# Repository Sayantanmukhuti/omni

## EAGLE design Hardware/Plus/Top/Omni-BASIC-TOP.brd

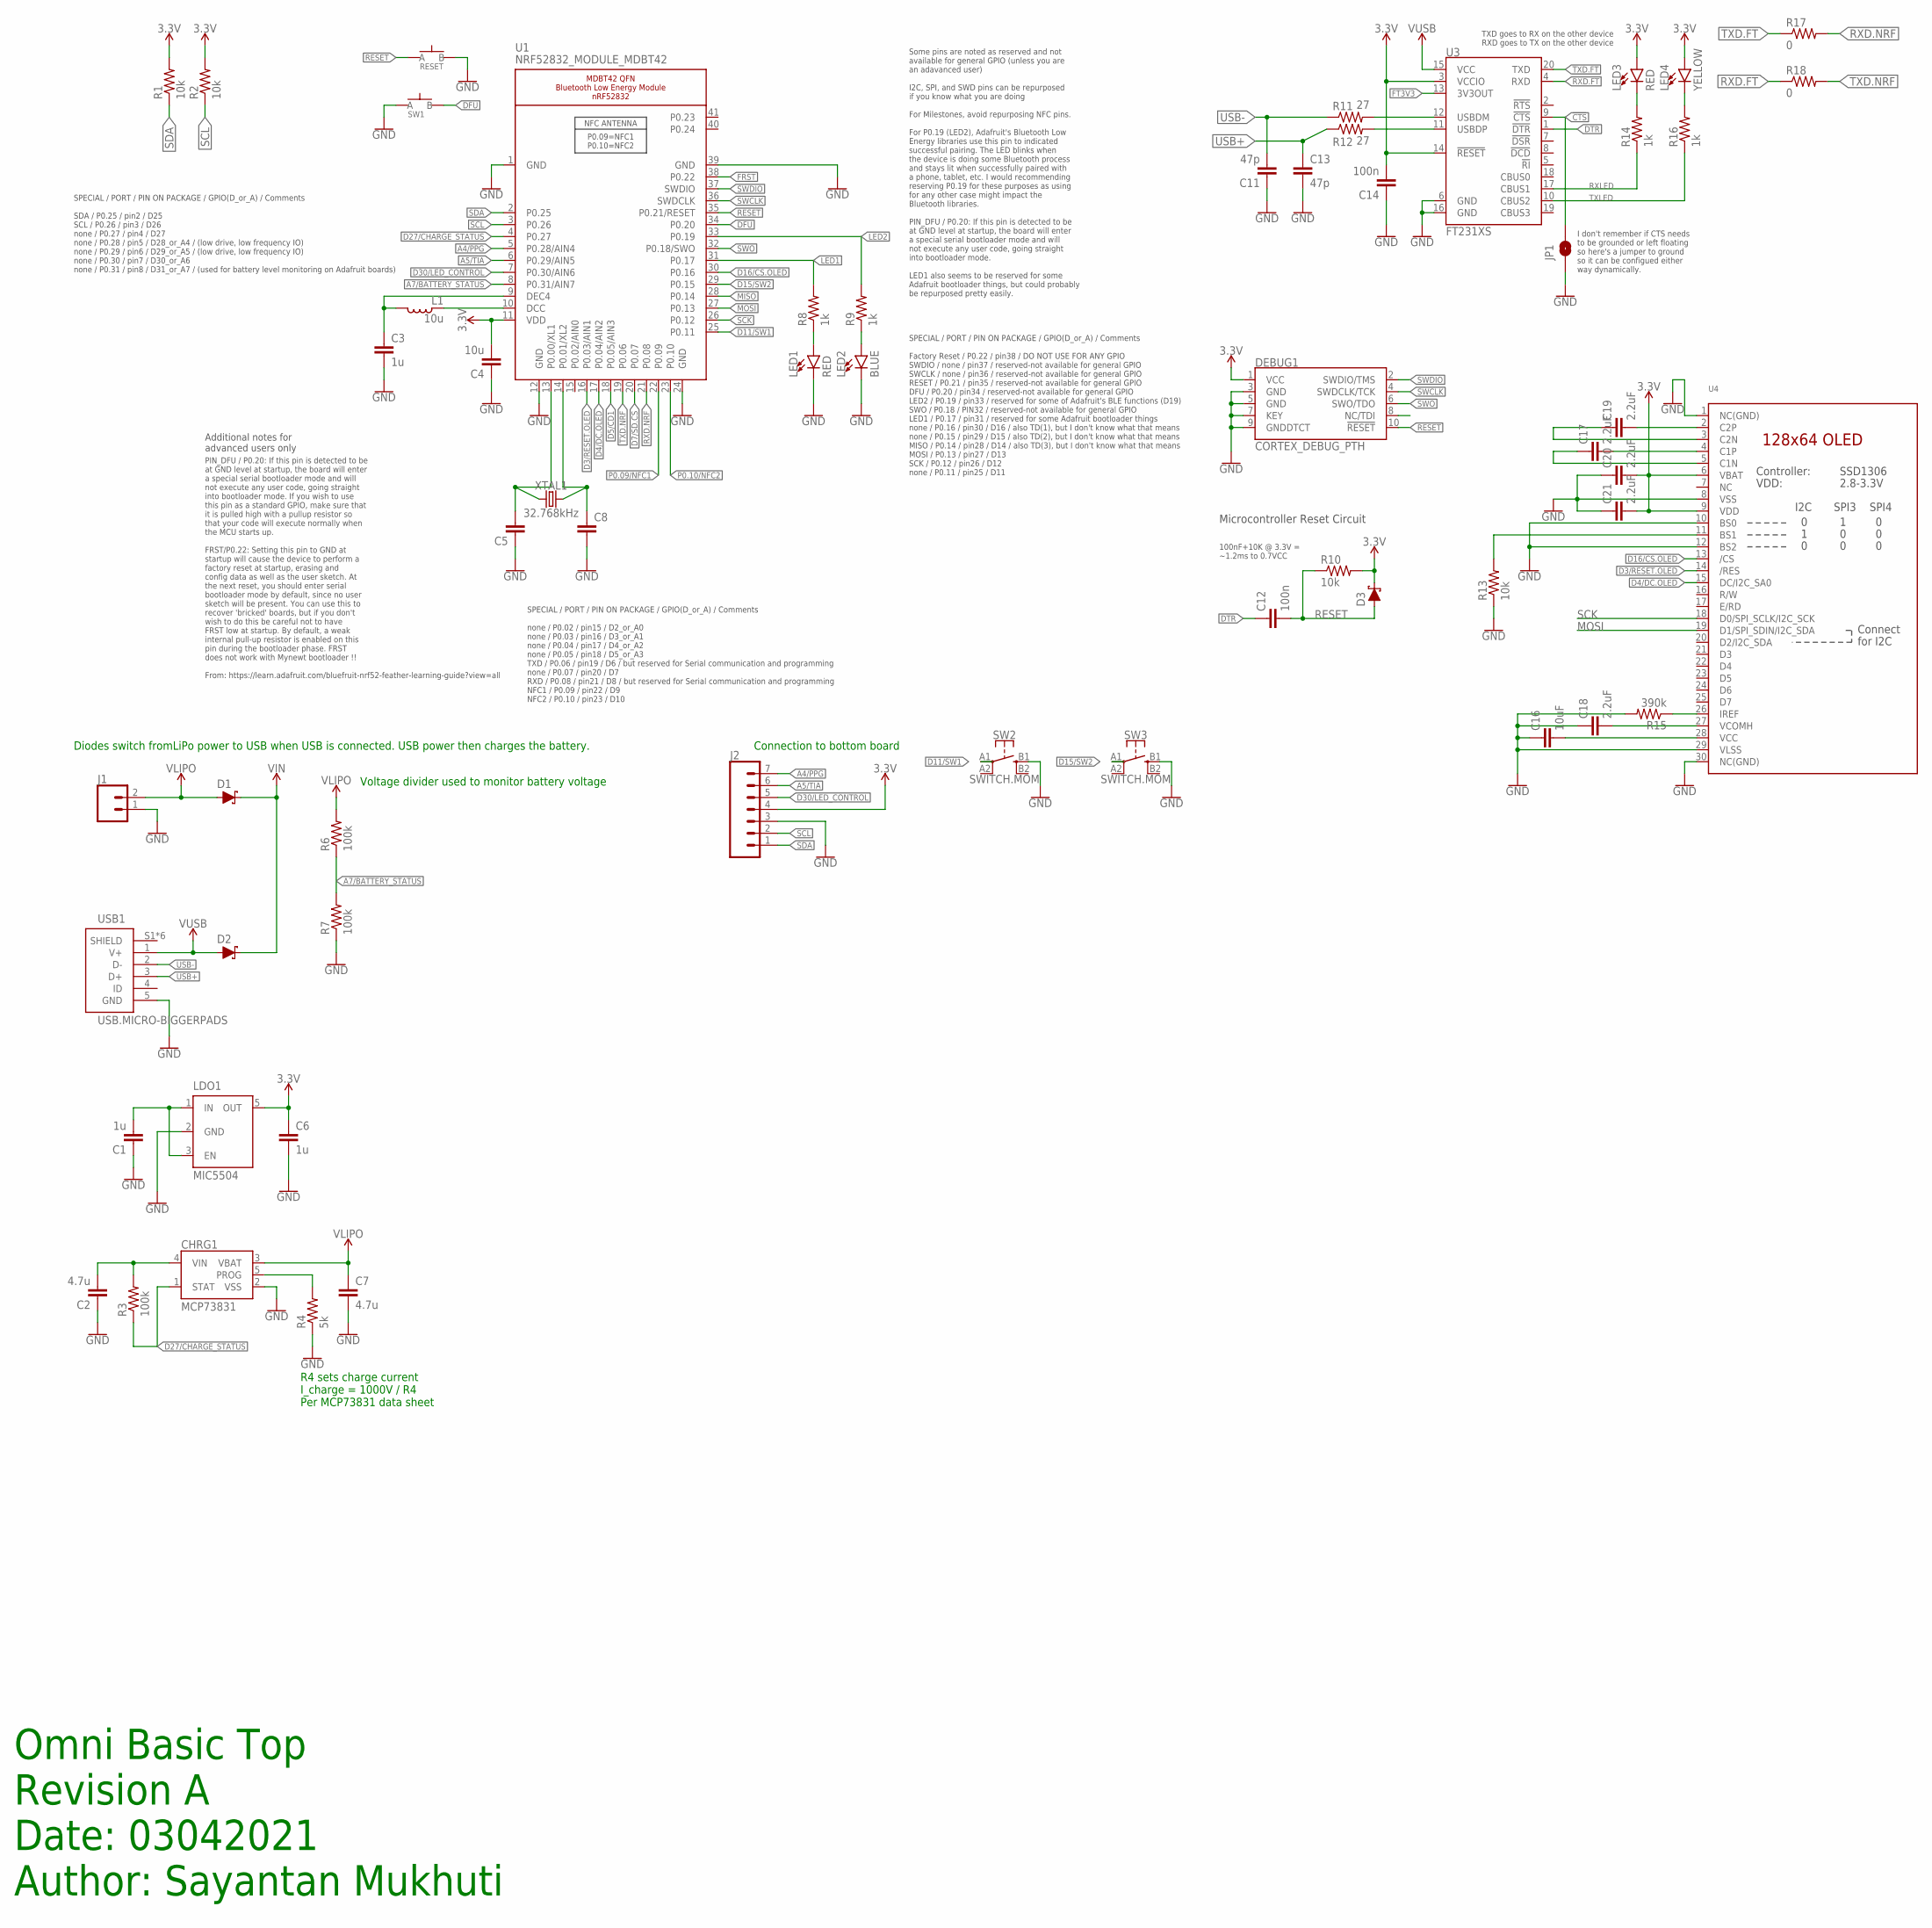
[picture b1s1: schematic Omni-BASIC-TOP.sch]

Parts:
C1, C3, C6: 1u; C0603
C2, C7: 4.7u; C0603
C4: 10u; C0805
C5, C8: CAPACITOR0603; C0603
C11, C13: 47p; C0603
C12, C14: 100n; C0603
C16: 10uF; C0603
C17, C18, C19, C20, C21: 2.2uF; C0402
CHRG1: MCP73831; SOT23-5
D1, D2, D3: SCHOTTKY-USC; USC
DEBUG1: CORTEX_DEBUG_PTH; 2X5-PTH-1.27MM
J1: CONN_02; 1X02
J2: CONN_07-1.27MM; 1X07_1.27MM
JP1: JUMPER-SMT_2_NO_SILK; SMT-JUMPER_2_NO_SILK
L1: 10u; L0603
LDO1: MIC5504; SOT23-5
LED1, LED3: RED; LED-0603
LED2: BLUE; LED-0603
LED4: YELLOW; LED-0603
R1, R2, R10, R13: 10k; R0603
R3, R6, R7: 100k; R0603
R4: 5k; R0603
R8, R9, R14, R16: 1k; R0603
R11, R12: 27; R0603
R15: 390k; R0603
R17, R18: 0; R0603
RESET: SPST-PTS830GG140-COPY.1-3; BUTTON-GULLWING
SW1: SPST-PTS830GG140-COPY.1-3; BUTTON-GULLWING
SW2, SW3: SWITCH.MOM; TACTILE_SWITCH_SMD_6.2MM_TALL
U1: NRF52832_MODULE_MDBT42; BLE_MODULE_RAYTAC_MDBT42
U3: FT231XS; SSOP20_L
U4: DISP_OLED_UG-2864HSWEG01-NO-WRAPAROUND; UG-2864HSWEG01_0.96IN_NO-WRAPAROUND
USB1: USB.MICRO-BIGGERPADS; USB-MICRO-01.BIGGERPADS
XTAL1: 32.768kHz; 2-SMD.NOLEAD.2.0MMTO1.2MM

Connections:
3.3V: C4.2, C6.1, C14.2, C20.2, C21.2, D3.- (C), DEBUG1.1 (VCC), J2.4, LDO1.5 (OUT), LED3.A, LED4.A, R1.2, R2.2, R10.2, U1.11 (VDD), U3.3 (VCCIO), U3.14 (!RESET), U4.6 (VBAT), U4.9 (VDD)
!CTS: JP1.2, U3.9 (!CTS)
A4/PPG: J2.7, U1.5 (P0.28/AIN4)
A5/TIA: J2.6, U1.6 (P0.29/AIN5)
A7/BATTERY_STATUS: R6.1, R7.2, U1.8 (P0.31/AIN7)
D3/RESET.OLED: U1.16 (P0.03/AIN1), U4.14 (/RES)
D4/DC.OLED: U1.17 (P0.04/AIN2), U4.15 (DC/I2C_SA0)
D5/CD1: U1.18 (P0.05/AIN3)
D7/SD.CS: U1.20 (P0.07)
D11/SW1: SW2.A1 (1), U1.25 (P0.11)
D15/SW2: SW3.A1 (1), U1.29 (P0.15)
D16/CS.OLED: U1.30 (P0.16), U4.13 (/CS)
D27/CHARGE_STATUS: CHRG1.1 (STAT), R3.1, U1.4 (P0.27)
D30/LED_CONTROL: J2.5, U1.7 (P0.30/AIN6)
DFU: SW1.3 (B), U1.34 (P0.20)
DTR: C12.1, U3.1 (!DTR)
FRST: U1.38 (P0.22)
FT3V3: U3.13 (3V3OUT)
GND: C1.1, C2.1, C3.2, C4.1, C5.1, C6.2, C7.2, C8.2, C11.1, C13.2, C14.1, C16.1, C18.1, C20.1, C21.1, CHRG1.2 (VSS), DEBUG1.3 (GND), DEBUG1.5 (GND), DEBUG1.7 (KEY), DEBUG1.9 (GNDDTCT), J1.1, J2.3, JP1.1, LDO1.2 (GND), LED1.C, LED2.C, R4.1, R7.1, R13.1, R15.2, RESET.3 (B), SW1.1 (A), SW2.B1 (3), SW3.B1 (3), U1.1 (GND), U1.12 (GND), U1.24 (GND), U1.39 (GND), U3.6 (GND), U3.16 (GND), U4.1 (NC(GND)), U4.8 (VSS), U4.10 (BS0), U4.12 (BS2), U4.29 (VLSS), U4.30 (NC(GND)), USB1.5 (GND)
LED1: R8.2, U1.31 (P0.17)
LED2: R9.2, U1.33 (P0.19)
MISO: U1.28 (P0.14)
MOSI: U1.27 (P0.13), U4.19 (D1/SPI_SDIN/I2C_SDA)
unnamed: R13.2, U4.11 (BS1)
unnamed: R15.1, U4.26 (IREF)
unnamed: C19.2, U4.2 (C2P)
unnamed: C5.2, U1.13 (P0.00/XL1), XTAL1.P$1 (1)
unnamed: C19.1, U4.3 (C2N)
unnamed: C8.1, U1.14 (P0.01/XL2), XTAL1.P$2 (2)
unnamed: C17.2, U4.4 (C1P)
unnamed: C17.1, U4.5 (C1N)
unnamed: LED1.A, R8.1
unnamed: LED2.A, R9.1
unnamed: L1.1, U1.10 (DCC)
unnamed: C3.1, L1.2, U1.9 (DEC4)
unnamed: C16.2, U4.28 (VCC)
unnamed: C18.2, U4.27 (VCOMH)
unnamed: CHRG1.5 (PROG), R4.2
unnamed: R11.2, U3.12 (USBDM)
unnamed: R12.2, U3.11 (USBDP)
unnamed: LED3.C, R14.2
unnamed: LED4.C, R16.2
P0.09/NFC1: U1.22 (P0.09)
P0.10/NFC2: U1.23 (P0.10)
RESET: C12.2, D3.+ (A), DEBUG1.10 (!RESET), R10.1, RESET.1 (A), U1.35 (P0.21/RESET)
RXD.FT: R18.1, U3.4 (RXD)
RXD.NRF: R17.2, U1.21 (P0.08)
RXLED: R14.1, U3.17 (CBUS1)
SCK: U1.26 (P0.12), U4.18 (D0/SPI_SCLK/I2C_SCK)
SCL: J2.2, R2.1, U1.3 (P0.26)
SDA: J2.1, R1.1, U1.2 (P0.25)
SWCLK: DEBUG1.4 (SWDCLK/TCK), U1.36 (SWDCLK)
SWDIO: DEBUG1.2 (SWDIO/TMS), U1.37 (SWDIO)
SWO: DEBUG1.6 (SWO/TDO), U1.32 (P0.18/SWO)
TXD.FT: R17.1, U3.20 (TXD)
TXD.NRF: R18.2, U1.19 (P0.06)
TXLED: R16.1, U3.10 (CBUS2)
USB+: C13.1, R12.1, USB1.3 (D+)
USB-: C11.2, R11.1, USB1.2 (D-)
VIN: C1.2, C2.2, CHRG1.4 (VIN), D1.- (C), D2.- (C), LDO1.1 (IN), LDO1.3 (EN), R3.2
VLIPO: C7.1, CHRG1.3 (VBAT), D1.+ (A), J1.2, R6.2
V_USB: D2.+ (A), U3.15 (VCC), USB1.1 (V+)

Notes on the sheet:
Microcontroller Reset Circuit
100nF+10K @ 3.3V = ~1.2ms to 0.7VCC
SPECIAL / PORT / PIN ON PACKAGE / GPIO(D_or_A) / Comments SDA / P0.25 / pin2 / D25 SCL / P0.26 / pin3 / D26 none / P0.27 / pin4 / D27 none / P0.28 / pin5 / D28_or_A4 / (low drive, low frequency IO) none / P0.29 / pin6 / D29_or_A5 / (low drive, low frequency IO) none / P0.30 / pin7 / D30_or_A6 none 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
SPECIAL / PORT / PIN ON PACKAGE / GPIO(D_or_A) / Comments none / P0.02 / pin15 / D2_or_A0 none / P0.03 / pin16 / D3_or_A1 none / P0.04 / pin17 / D4_or_A2 none / P0.05 / pin18 / D5_or_A3 TXD / P0.06 / pin19 / D6 / but reserved for Serial communication and programming none / P0.07 / pin20 / D7 RXD / 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
SPECIAL / PORT / PIN ON PACKAGE / GPIO(D_or_A) / Comments Factory Reset / P0.22 / pin38 / DO NOT USE FOR ANY GPIO SWDIO / none / pin37 / reserved-not available for general GPIO SWCLK / none / pin36 / reserved-not available for general GPIO RESET / P0.21 / pin35 / reserved-not available for general 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
Some pins are noted as reserved and not available for general GPIO (unless you are an adavanced user) I2C, SPI, and SWD pins can be repurposed if you know what you are doing For Milestones, avoid repurposing NFC pins. For P0.19 (LED2), Adafruit's Bluetooth Low Energy libraries use this pin to indic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
PIN_DFU / P0.20: If this pin is detected to be at GND level at startup, the board will enter a special serial bootloader mode and will not execute any user code, going straight into bootloader mode. If you wish to use this pin as a standard GPIO, make sure that it is pulled high with a pullup resis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
Additional notes for advanced users only
TXD goes to RX on the other device RXD goes to TX on the other device
I don't remember if CTS needs to be grounded or left floating so here's a jumper to ground so it can be configued either way dynamically.
Connection to bottom board
Omni Basic Top Revision A Date: 03042021 Author: Sayantan Mukhuti
Diodes switch fromLiPo power to USB when USB is connected. USB power then charges the battery.
R4 sets charge current I_charge = 1000V / R4 Per MCP73831 data sheet
Voltage divider used to monitor battery voltage

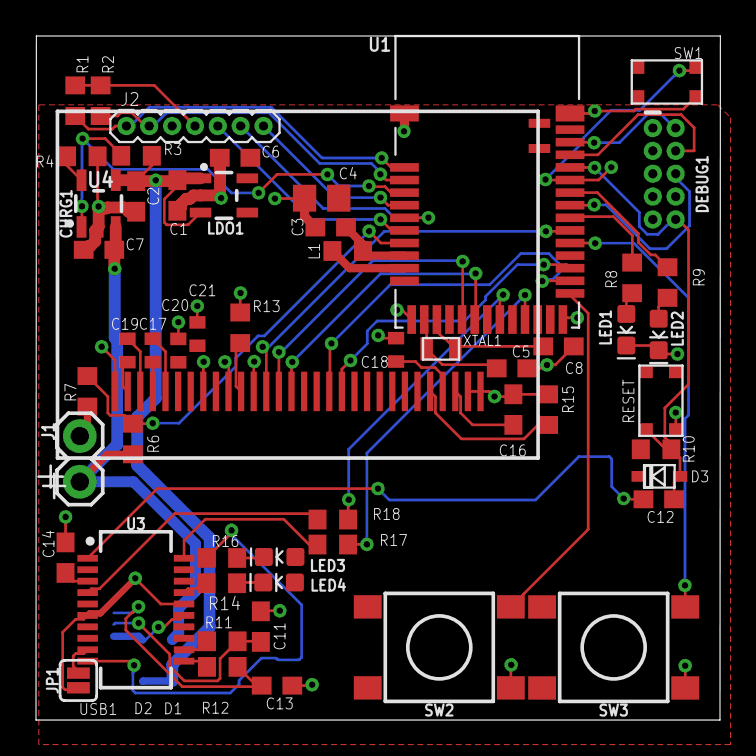
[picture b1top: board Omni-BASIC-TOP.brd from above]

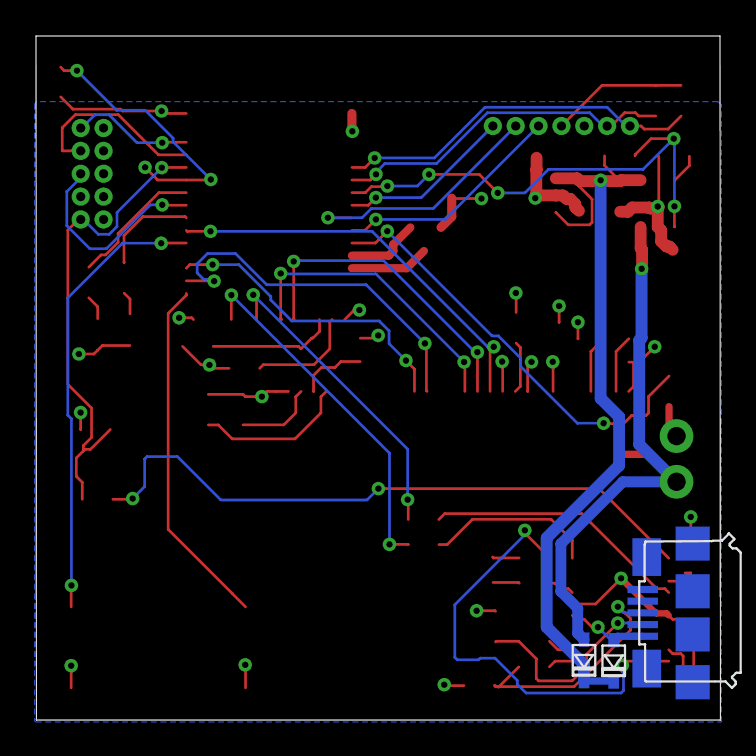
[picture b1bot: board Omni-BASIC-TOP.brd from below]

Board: 2 copper layers, 38.0 x 38.0 mm, 58 parts (3 on the bottom side), 55 nets.

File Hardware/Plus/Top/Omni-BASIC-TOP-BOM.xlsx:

Omni Basic Top Board Rev A / Purdue Milestones |  |  |  |  |  |  |  |  |  |  | Total | 93.235600000000005 | Total (in Bulk) | 0.19009999999999999
BOM # | Comment | Designator | Description | Mounting Type | Package | Manufacturer | Manufacturer Part Number | Supplier | Supplier Part Number | Price per unit | Quantity | Total | Per 100 | Total
1 | 1uF capacitor | C1, C3, C6 | 1µF ±10% 25V Ceramic Capacitor X5R 0603 (1608 Metric) | SMD | 0603 | Samsung Electro-Mechanics | CL10A105KA8NNNC | Digi-Key | 1276-1102-1-ND | 0.1 | 3 | 0.30000000000000004 | 1.8499999999999999E-2 | 5.5499999999999994E-2
2 | 4.7 uF Capacitor | C1, C7 | red 622nm LED Indication - Discrete 2.2V 0603 (1608 Metric) | SMD | 0603 | Samsung Electro-Mechanics | CL10A475KO8NNNC | Digi-Key | 1276-1784-1-ND | 4.3999999999999997E-2 | 2 | 8.7999999999999995E-2 |  | 0
3 | 10 uF 0603 Capacitor | C4, C16 | 10µF ±10% 10V Ceramic Capacitor X5R 0603 (1608 Metric) | SMD | 0603 | Murata Electronics | GRM188R61A106KE69J | Digi-Key | 490-14372-1-ND | 6.3200000000000006E-2 | 2 | 0.12640000000000001 |  | 0
4 | 12pF capacitor | C5, C8 | 12pF ±5% 50V Ceramic Capacitor C0G, NP0 0603 (1608 Metric) | SMD | 0603 | Walsin Technology Corporation | 0603N120J500CT | Digi-Key | 1292-1480-1-ND | 1.1900000000000001E-2 | 2 | 2.3800000000000002E-2 |  | 0
5 | 47 pF Capacitor | C11, C13 | 47pF ±5% 50V Ceramic Capacitor C0G, NP0 0603 (1608 Metric) | SMD | 0603 | Walsin Technology Corporation | 0603N470J500CT | Digi-Key | 1292-1528-1-ND | 1.0999999999999999E-2 | 2 | 2.1999999999999999E-2
6 | 100 nF Capacitor | C12, C14 | 0.1µF ±5% 16V Ceramic Capacitor X7R 0603 (1608 Metric) | SMD | 0603 | Yageo | CC0603JRX7R7BB104 | Digi-Key | 311-1776-1-ND | 3.3099999999999997E-2 | 2 | 6.6199999999999995E-2
7 | 2.2u capacitor | C17, C18, C19, C20, C21 | 2.2µF ±10% 16V Ceramic Capacitor X5R 0603 (1608 Metric) | SMD | 0603 | Samsung Electro-Mechanics | CL10A225KO8NNNC | Digi-Key | 1276-1040-1-ND | 3.1600000000000003E-2 | 5 | 0.15800000000000003 |  | 0
8 | MCP73831 T Li-Ion, Li-Pol Controller | CHRG1 | Charger IC Lithium-Ion/Polymer SOT-23-5 | SMD | SOT-23-5 | Microchip Technology | MCP73831T-2ACI/OT | Digi-Key | MCP73831T-2ACI/OTCT-ND | 0.56000000000000005 | 1 | 0.56000000000000005
9 | Schottky Diode | D1, D2, D3 | Diode Schottky 30V 1.5A Surface Mount USC | SMD | USC | Toshiba Semiconductor and Storage | CUS15S30,H3F | Digi-Key | CUS15S30H3FCT-ND | 0.25600000000000001 | 3 | 0.76800000000000002
10 | Cortex Debug Connector - 10 pin | DEBUG1 CORTEX_DEBUG_PTH | Connector Header Through Hole 10 position 0.050" (1.27mm) | THT | NA | Amphenol ICC (FCI) | 20021111-00010T4LF | Digi-Key | 609-3712-ND | 0.69 | 1 | 0.69
11 | 10µH Inductor | L1 | 10µH Shielded Multilayer Inductor 250mA 1.05Ohm 0603 (1608 Metric) | SMD | 0603 | TDK Corporation | MLZ1608M100WTD25 | Digi-Key | MLZ1608M100WTD25 | 0.22 | 1 | 0.22 | 0.1346 | 0.1346
12 | MIC5504 Voltage Regulator | LD01 | Linear Voltage Regulator IC 1 Output 300mA SOT-23-5 | SMD | SOT23-5 | Microchip Technology | MIC5504-3.3YM5-TR | Digi-Key | 576-4764-1-ND | 0.11 | 1 | 0.11
13 | Red LED | LED1, LED3 | Red 622nm LED Indication - Discrete 2.2V 0603 (1608 Metric) | SMD | 0603 | Inolux | IN-S63ATR | Digi-Key | 1830-1065-1-ND | 0.17699999999999999 | 2 | 0.35399999999999998
14 | Blue LED | LED2 | Blue 470nm LED Indication - Discrete 3V 0603 (1608 Metric) | SMD | 0603 | Inolux | IN-S63AT5B | Digi-Key | 1830-1061-1-ND | 0.17699999999999999 | 1 | 0.17699999999999999
15 | Yellow LED | LED4 | Yellow 590nm LED Indication - Discrete 2V 0603 (1608 Metric) | SMD | 0603 | Wurth Electronics Inc. | 150060YS75000 | Digi-Key | 732-4981-1-ND | 0.14000000000000001 | 1 | 0.14000000000000001
16 | 10k Resistor | R1, R2, R10, R13 | 10 kOhms ±1% 0.1W, 1/10W Chip Resistor 0603 (1608 Metric) Automotive AEC-Q200 T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 | SMD | 0603 | Stackpole Electronics Inc | RMCF0603FT10K0 | Digi-Key | RMCF0603FT10K0CT-ND | 5.8999999999999999E-3 | 4 | 2.3599999999999999E-2
17 | 100k Resistor | R3, R6, R7 | 100 kOhms ±1% 0.1W, 1/10W Chip Resistor 0603 (1608 Metric) Automotive AEC-Q200 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 | SMD | 0603 | Stackpole Electronics Inc | RMCF0603FT100K | Digi-Key | RMCF0603FT100KCT-ND | 5.8999999999999999E-3 | 3 | 1.77E-2
18 | 1k Resistor | R8, R9, R14, R16 | 1 kOhms ±1% 0.1W, 1/10W Chip Resistor 0603 (1608 Metric) Automotive AEC-Q200 Th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 | SMD | 0603 | Stackpole Electronics Inc | RMCF0603FT1K00 | Digi-Key | RMCF0603FT1K00CT-ND | 5.8999999999999999E-3 | 4 | 2.3599999999999999E-2
19 | 27 ohm resistor | R11, R12 | 27 Ohms ±1% 0.1W, 1/10W Chip Resistor 0603 (1608 Metric) Automotive AEC-Q200 Th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 | SMD | 0603 | Stackpole Electronics Inc | RMCF0603FT27R0 | Digi-Key | RMCF0603FT27R0CT-ND | 5.8999999999999999E-3 | 2 | 1.18E-2
20 | 390k resistor | R15 | 390 kOhms ±1% 0.1W, 1/10W Chip Resistor 0603 (1608 Metric) Automotive AEC-Q200 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 | SMD | 0603 | Stackpole Electronics Inc | RMCF0603FG390K | Digi-Key | RMCF0603FG390KCT-ND | 5.8999999999999999E-3 | 1 | 5.8999999999999999E-3
21 | Tiny Rectangular Button | RESET, SW1 | Tactile Switch SPST-NO Top Actuated Surface Mount | SMD | Gull Wing | C&K Components | PTS830GM140 SMTR LFS | Digi-Key | CKN10587CT-ND | 0.56000000000000005 | 2 | 0.56000000000000005 |  | 0
22 | SWITCH.MOM (TACTILE_SWITCH_SMD_6.2MM_TALL) | SW2, SW3 | Tactile Switch SPST-NO Top Actuated Surface Mount - TACT 4.5 X 4.5, 3.8 MM H, 1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 | SMD | Gull Wing | C&K | PTS 647 SM38 SMTR2 LFS | Digi-Key | PTS647SM38SMTR2LFSCT-ND | 0.1208 | 2 | 0.24160000000000001
23 | NRF52832_MODULE_MDBT42 | U1 | Bluetooth Bluetooth v4.2 Transceiver Module 2.4GHz Integrated, Chip Surface Mou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 | SMD | 41-SMD Module | Seeed Technology Co., Ltd | 317030213 | Digi-Key | 1597-1434-ND | 10.1 | 1 | 10.1
24 | FT231XS USB Serial | U3 | USB Bridge, USB to UART USB 2.0 UART Interface 20-SSOP | SMD | 20-SSOP | FTDI, Future Technology Devices International Ltd | FT231XS-U | Digi-Key | 768-1156-5-ND | 2.12 | 1 | 2.12
25 | 0.96" OLED | U4 | Datasheet 128x64 OLED Module SPI 0.96"Graphic Displays,White on Black | SMD | Flexible Connector | EastRising | https://www.buydisplay.com/datasheet-128x64-oled-module-spi-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 | BuyDisplay.com | https://www.buydisplay.com/datasheet-128x64-oled-module-spi-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 | 2.5099999999999998 | 1 | 75.3
26 | Micro USB | USB1 | USB - micro B USB 2.0 Receptacle Connector 5 Position Surface Mount, Right Angle | SMD | Flange, Horizontal | Amphenol FCI | 10118192-0001LF | Digi-Key | 609-4613-1-ND | 0.43 | 1 | 0.43
27 | CRYSTALECS-.327-12.5-12-C-TR (CRYSTAL) (32.7680kHz) | XTAL1 | 32.768kHz ±10ppm Crystal 12.5pF 90 kOhms 2-SMD, No Lead | SMD | 2-SMD, No Lead | ECS Inc. | ECS-.327-12.5-12-C-TR | Digi-Key | XC2288CT-ND | 0.59799999999999998 | 1 | 0.59799999999999998

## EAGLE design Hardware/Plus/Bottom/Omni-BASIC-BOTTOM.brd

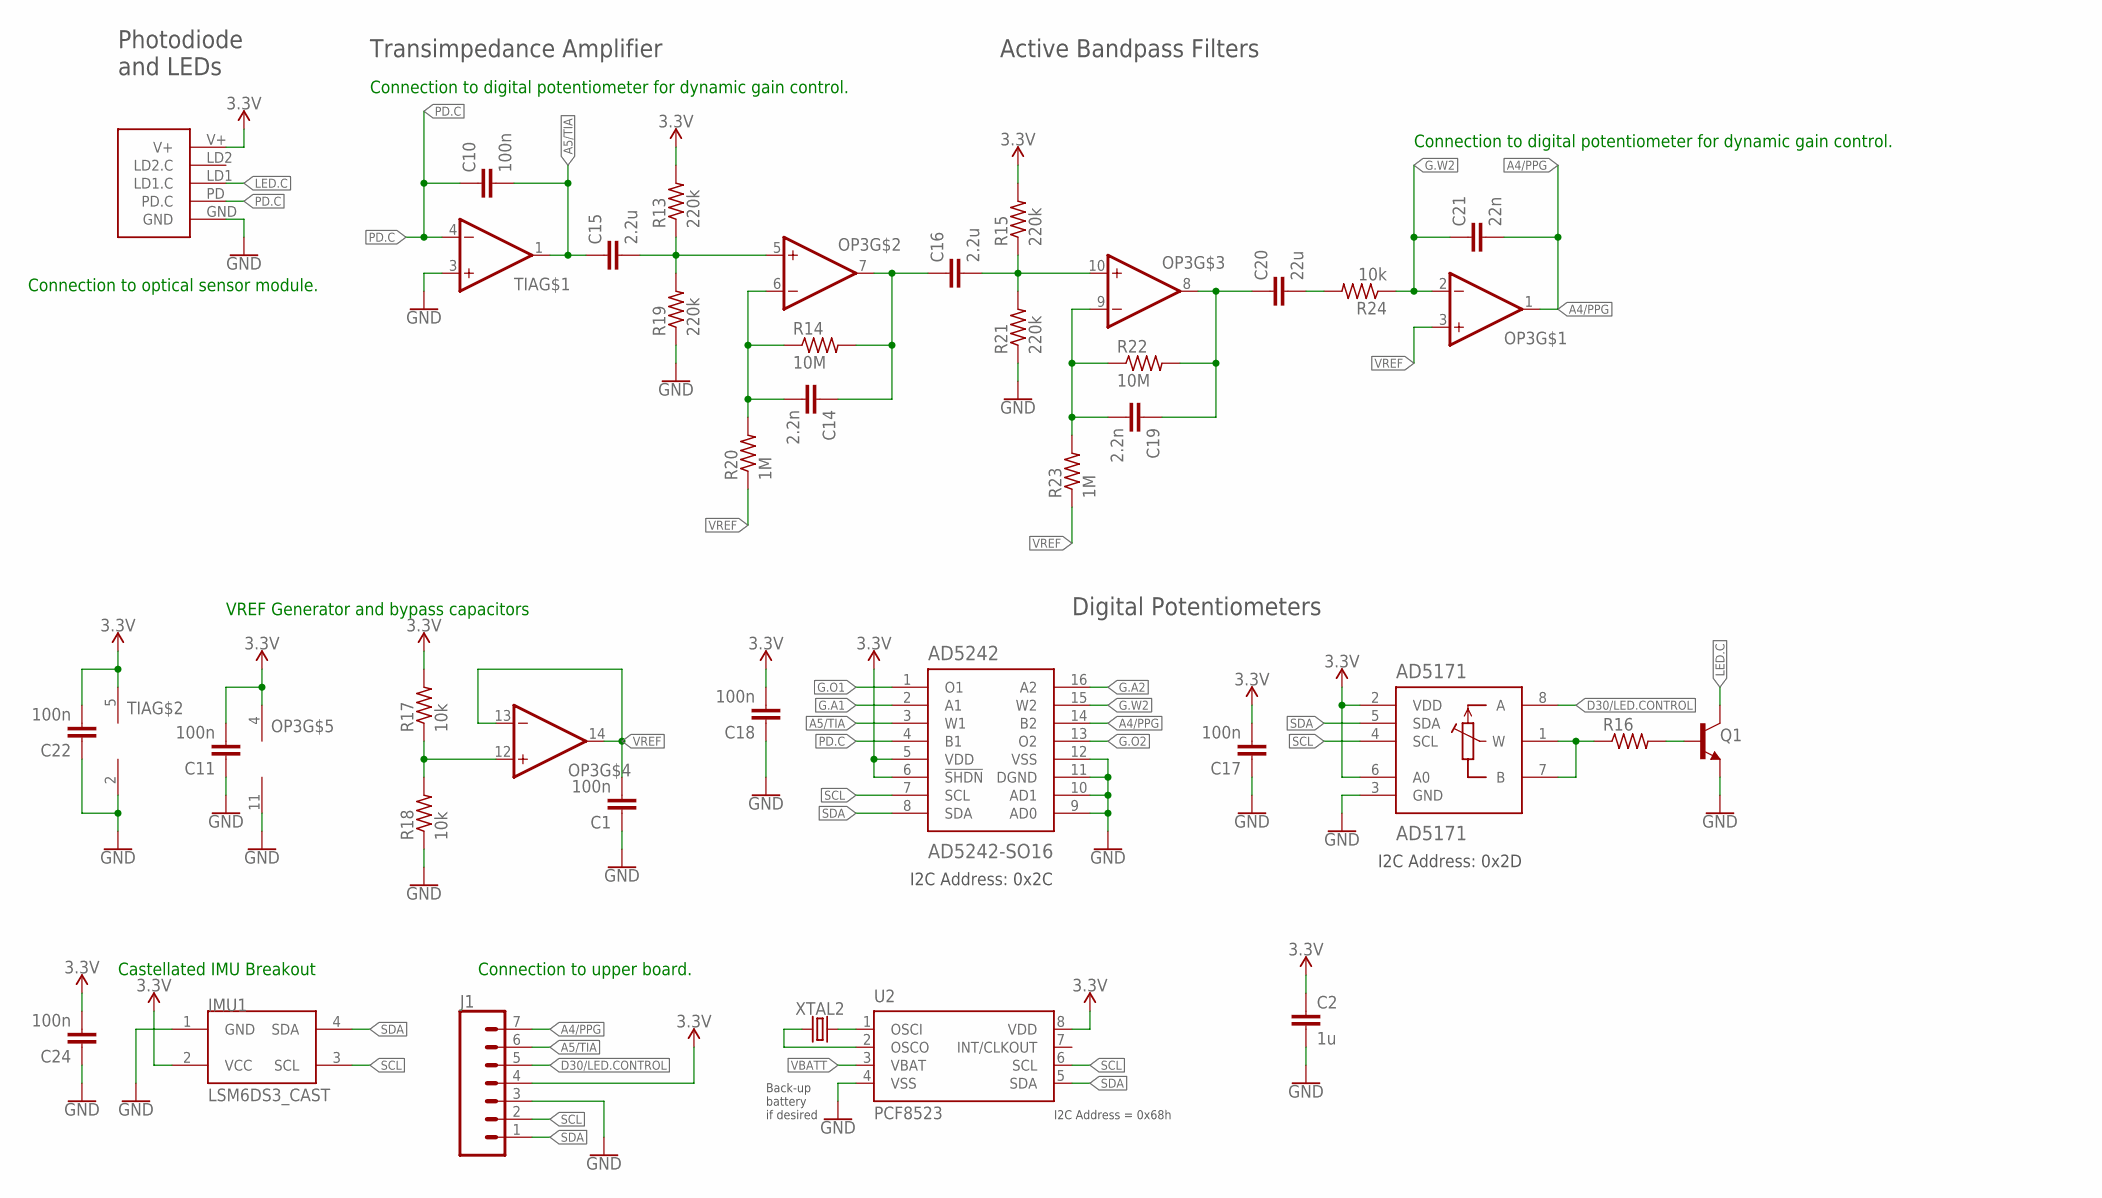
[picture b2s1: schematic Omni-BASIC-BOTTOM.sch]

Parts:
AD5171: AD5171; SOT-23-8
AD5242: AD5242-SO16; SO16
C1, C10, C11, C17, C18, C22, C24: 100n; C0603
C2: 1u; C0603
C14, C19: 2.2n; C0603
C15, C16: 2.2u; C0603
C20: 22u; C0603
C21: 22n; C0603
IMU1: LSM6DS3_CAST
J1: CONN_07-1.27MM; 1X07_1.27MM
OP3: OP-QUAD-SO14; SO14
Q1: NPN-GENERIC; SOT23-3
R13, R15, R19, R21: 220k; R0603
R14, R22: 10M; R0603
R16: RESISTOR0603; R0603
R17, R18: 10k; R0402
R20, R23: 1M; R0603
R24: 10k; R0603
TIA: OP-SINGLEOT; SOT23-5
U2: PCF8523; SO8; DIGIKEY 568-5306-1-ND
U$3: PPG.MODULE.2
XTAL2: 32.7680kHz; 2-SMD.NOLEAD.2.0MMTO1.2MM

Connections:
3.3V: AD5171.2 (VDD), AD5171.6 (A0), AD5242.5 (VDD), AD5242.6 (!SHDN), C2.1, C11.2, C17.2, C18.2, C22.2, C24.2, IMU1.2 (VCC), J1.4, OP3.4 (V+), R13.2, R15.2, R17.2, TIA.5 (V+), U2.8 (VDD), U$3.V+
A4/PPG: AD5242.14 (B2), C21.2, J1.7, OP3.1 (OUT)
A5/TIA: AD5242.3 (W1), C10.2, C15.1, J1.6, TIA.1 (OUT)
D30/LED.CONTROL: AD5171.8 (A), J1.5
G.A1: AD5242.2 (A1)
G.A2: AD5242.16 (A2)
G.O1: AD5242.1 (O1)
G.O2: AD5242.13 (O2)
G.W2: AD5242.15 (W2), C21.1, OP3.2 (-IN), R24.1
GND: AD5171.3 (GND), AD5242.9 (AD0), AD5242.10 (AD1), AD5242.11 (DGND), AD5242.12 (VSS), C1.1, C2.2, C11.1, C17.1, C18.1, C22.1, C24.1, IMU1.1 (GND), J1.3, OP3.11 (V-), Q1.2 (E), R18.1, R19.1, R21.1, TIA.2 (V-), TIA.3 (+IN), U2.4 (VSS), U$3.GND
LED.C: Q1.3 (C), U$3.LD1 (LD1.C)
unnamed: U2.2 (OSCO), XTAL2.P$1 (1)
unnamed: U2.1 (OSCI), XTAL2.P$2 (2)
unnamed: Q1.1 (B), R16.2
unnamed: AD5171.1 (W), AD5171.7 (B), R16.1
unnamed: OP3.12 (+IN), R17.1, R18.2
unnamed: C15.2, OP3.5 (+IN), R13.1, R19.2
unnamed: C14.2, OP3.6 (-IN), R14.1, R20.2
unnamed: C14.1, C16.1, OP3.7 (OUT), R14.2
unnamed: C16.2, OP3.10 (+IN), R15.1, R21.2
unnamed: C19.2, OP3.9 (-IN), R22.1, R23.2
unnamed: C19.1, C20.1, OP3.8 (OUT), R22.2
unnamed: C20.2, R24.2
PD.C: AD5242.4 (B1), C10.1, TIA.4 (-IN), U$3.PD (PD.C)
SCL: AD5171.4 (SCL), AD5242.7 (SCL), IMU1.3 (SCL), J1.2, U2.6 (SCL)
SDA: AD5171.5 (SDA), AD5242.8 (SDA), IMU1.4 (SDA), J1.1, U2.5 (SDA)
VBATT: U2.3 (VBAT)
VREF: C1.2, OP3.3 (+IN), OP3.13 (-IN), OP3.14 (OUT), R20.1, R23.1

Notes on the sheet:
Photodiode and LEDs
Active Bandpass Filters
Digital Potentiometers
Transimpedance Amplifier
I2C Address: 0x2C
I2C Address: 0x2D
Connection to optical sensor module.
Connection to digital potentiometer for dynamic gain control.
Connection to upper board.
Castellated IMU Breakout
VREF Generator and bypass capacitors
I2C Address = 0x68h
Back-up battery if desired

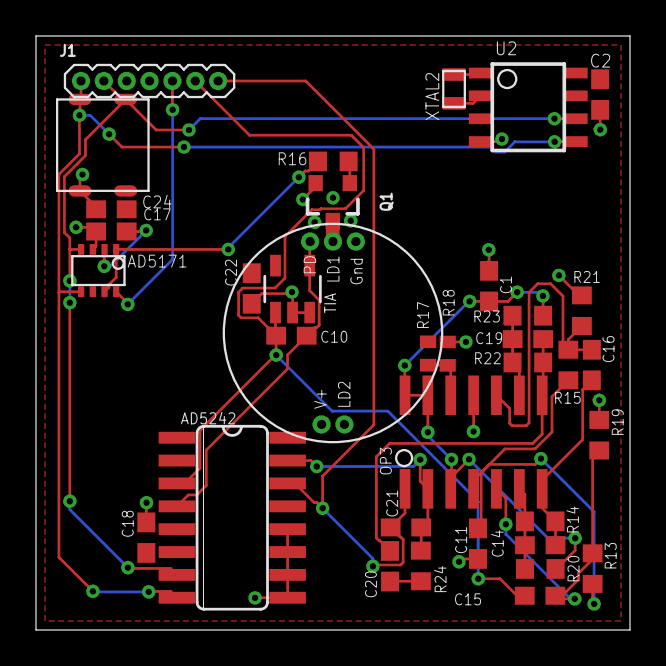
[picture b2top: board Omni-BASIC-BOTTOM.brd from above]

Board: 2 copper layers, 33.0 x 33.0 mm, 36 parts (0 on the bottom side), 23 nets.

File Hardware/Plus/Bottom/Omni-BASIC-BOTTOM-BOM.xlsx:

Omni Basic Bottom Board Rev A / Purdue Milestones |  |  |  |  |  |  |  |  |  |  | Total | 91.178000000000011 | Total (in Bulk) | 1.8499999999999999E-2
BOM # | Comment | Designator | Description | Mounting Type | Package | Manufacturer | Manufacturer Part Number | Supplier | Supplier Part Number | Price per unit | Quantity | Total | Per 100 | Total
1 | AD5171 | AD5171 | Digital Potentiometer ICs IC 6-Bit OTP I2C | SMD | SOT-23-8 | Analog Devices | AD5171BRJZ100-R7 | Mouser | 584-AD5171BRJZ100-R7 | 2.68 | 5 | 13.4 |  | 0
2 | AD5242 | AD5242 | Digital Potentiometer 1M Ohm 2 Circuit 256 Taps I²C Interface 16-SOIC | SMD | 16-SOIC | Analog Devices Inc. | AD5242BRZ1M | Digi-Key | AD5242BRZ1M-ND | 3.47 | 6 | 20.82
3 | 100 nF Capacitor | C1, C10, C11, C17, C18, C22, C24 | 0.1µF ±5% 16V Ceramic Capacitor X7R 0603 (1608 Metric) | SMD | 0603 | Yageo | CC0603JRX7R7BB104 | Digi-Key | 311-1776-1-ND | 3.3099999999999997E-2 | 100 | 3.3099999999999996
4 | 1uF capacitor | C2 | 1µF ±10% 25V Ceramic Capacitor X5R 0603 (1608 Metric) | SMD | 0603 | Samsung Electro-Mechanics | CL10A105KA8NNNC | Digi-Key | 1276-1102-1-ND | 0.1 | 1 | 0.1 | 1.8499999999999999E-2 | 1.8499999999999999E-2
5 | 2.2n Capacitor | C14, C19 | 2200pF ±10% 50V Ceramic Capacitor X7R 0603 (1608 Metric) | SMD | 0603 | Walsin Technology Corporation | 0603B222K500CT | Digi-Key | 1292-1412-1-ND | 1.1599999999999999E-2 | 100 | 1.1599999999999999
6 | 2.2u capacitor | C15, C16 | 2.2µF ±10% 16V Ceramic Capacitor X5R 0603 (1608 Metric) | SMD | 0603 | Samsung Electro-Mechanics | CL10A225KO8NNNC | Digi-Key | 1276-1040-1-ND | 3.1600000000000003E-2 | 100 | 3.16 |  | 0
7 | 22u capacitor | C20 | 22µF ±20% 10V Ceramic Capacitor X5R 0603 (1608 Metric) | SMD | 0603 | Samsung Electro-Mechanics | CL10A226MP8NUNE | Digi-Key | 1276-1274-1-ND | 6.7199999999999996E-2 | 100 | 6.72 |  | 0
8 | 22n capacitor | C21 | 0.022µF ±10% 50V Ceramic Capacitor X7R 0603 (1608 Metric) | SMD | 0603 | Samsung Electro-Mechanics | CL10B223KB8NNNC | Digi-Key | 1276-1104-1-ND | 1.5599999999999999E-2 | 100 | 1.5599999999999998
9 | LSM6DS3 castellated breakout |  |  |  |  |  |  |  |  |  |  | 0 |  | 0
10 | Op Amp - MCP6004 | OP3 | General Purpose Amplifier 4 Circuit Rail-to-Rail 14-SOIC | SMD | 14-SOIC | Microchip Technology | MCP6004T-I/SL | Digi-Key | MCP6004T-I/SLCT-ND | 0.44 | 6 | 2.64
11 | NPN-Generic | Q1 | Bipolar (BJT) Transistor NPN 40V 600mA 300MHz 250mW Surface Mount TO-236AB | SMD | TO-236AB | Nexperia USA Inc. | PMBT2222A,215 | Digi-Key | 1727-2956-1-ND | 1.05 | 10 | 10.5
12 | 220k resistor | R13, R15, R19, R21 | 220 kOhms ±1% 0.1W, 1/10W Chip Resistor 0603 (1608 Metric) Automotive AEC-Q200 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 | SMD | 0603 | Stackpole Electronics Inc | RMCF0603FT220K | Digi-Key | RMCF0603FT220KCT-ND | 5.8999999999999999E-3 | 100 | 0.59
13 | 10M Resistor | R14, R22 | 10 MOhms ±1% 0.1W, 1/10W Chip Resistor 0603 (1608 Metric) Automotive AEC-Q200 T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 | SMD | 0603 | Stackpole Electronics Inc | RMCF0603FT10M0 | Digi-Key | RMCF0603FT10M0CT-ND | 8.8999999999999999E-3 | 100 | 0.89
14 | 10k Resistor | R17, R18, R24 | 10 kOhms ±1% 0.1W, 1/10W Chip Resistor 0603 (1608 Metric) Automotive AEC-Q200 T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 | SMD | 0603 | Stackpole Electronics Inc | RMCF0603FT10K0 | Digi-Key | RMCF0603FT10K0CT-ND | 5.8999999999999999E-3 | 100 | 0.59
15 | 1M Resistor | R20, R23 | 1 MOhms ±1% 0.1W, 1/10W Chip Resistor 0603 (1608 Metric) Automotive AEC-Q200 Th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 | SMD | 0603 | Stackpole Electronics Inc | RMCF0603FT1M00 | Digi-Key | RMCF0603FT1M00CT-ND | 5.8999999999999999E-3 | 100 | 0.59
16 | TIA | TIA | General Purpose Amplifier 1 Circuit Rail-to-Rail SOT-23-5 | SMD | SOT-23-5 | Microchip Technology | MCP6001T-I/OT | Digi-Key | MCP6001T-I/OTCT-ND | 0.24 | 6 | 1.44
17 | CONN_07-1.27MM | U$3 | 50 Positions Header Connector 0.050" (1.27mm) Through Hole Gold | THT |  | Sullins Connector Solutions | GRPB501VWVN-RC | Digi-Key | S9014E-50-ND | 3.11 | 5 | 15.549999999999999
18 | PCF8523 | U2 | Real Time Clock (RTC) IC Clock/Calendar I²C, 2-Wire Serial 8-SOIC (0.154", 3.90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 | SMD | 8-SO | NXP USA Inc. | PCF8523T/1,118 | Digi-Key | 568-5306-1-ND | 1.26 | 6 | 7.5600000000000005
19 | CRYSTALECS-.327-12.5-12-C-TR (CRYSTAL) (32.7680kHz) | XTAL2 | 32.768kHz ±10ppm Crystal 12.5pF 90 kOhms 2-SMD, No Lead | SMD | 2-SMD, No Lead | ECS Inc. | ECS-.327-12.5-12-C-TR | Digi-Key | XC2288CT-ND | 0.59799999999999998 | 1 | 0.59799999999999998

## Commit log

2021-02-06 New File
2021-02-13 Today's work
2021-02-20 commit operation
2021-02-27 Latest Update
2021-03-20 End of class update
2021-03-27 Update 2703-1
2021-03-27 Fixed 1 of 2 airwires update
2021-04-03 3rd April Update 1
